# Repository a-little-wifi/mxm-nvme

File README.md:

# MXM NVMe

I made an MXM edge connector footprint and wanted to make a board that uses it so I can make some screenshots, so here's a crappy unfinished concept for a board that lets you use one or maybe more NVMe SSDs in an MXM slot. Currently wired for x8x4x4 bifurcation mode.

Feel free to take the MXM edge connector footprint from it.

## Here's some pictures
<!------>

I didn't do impedance matching or anything yet, the diffpairs are just there to look pretty ✨

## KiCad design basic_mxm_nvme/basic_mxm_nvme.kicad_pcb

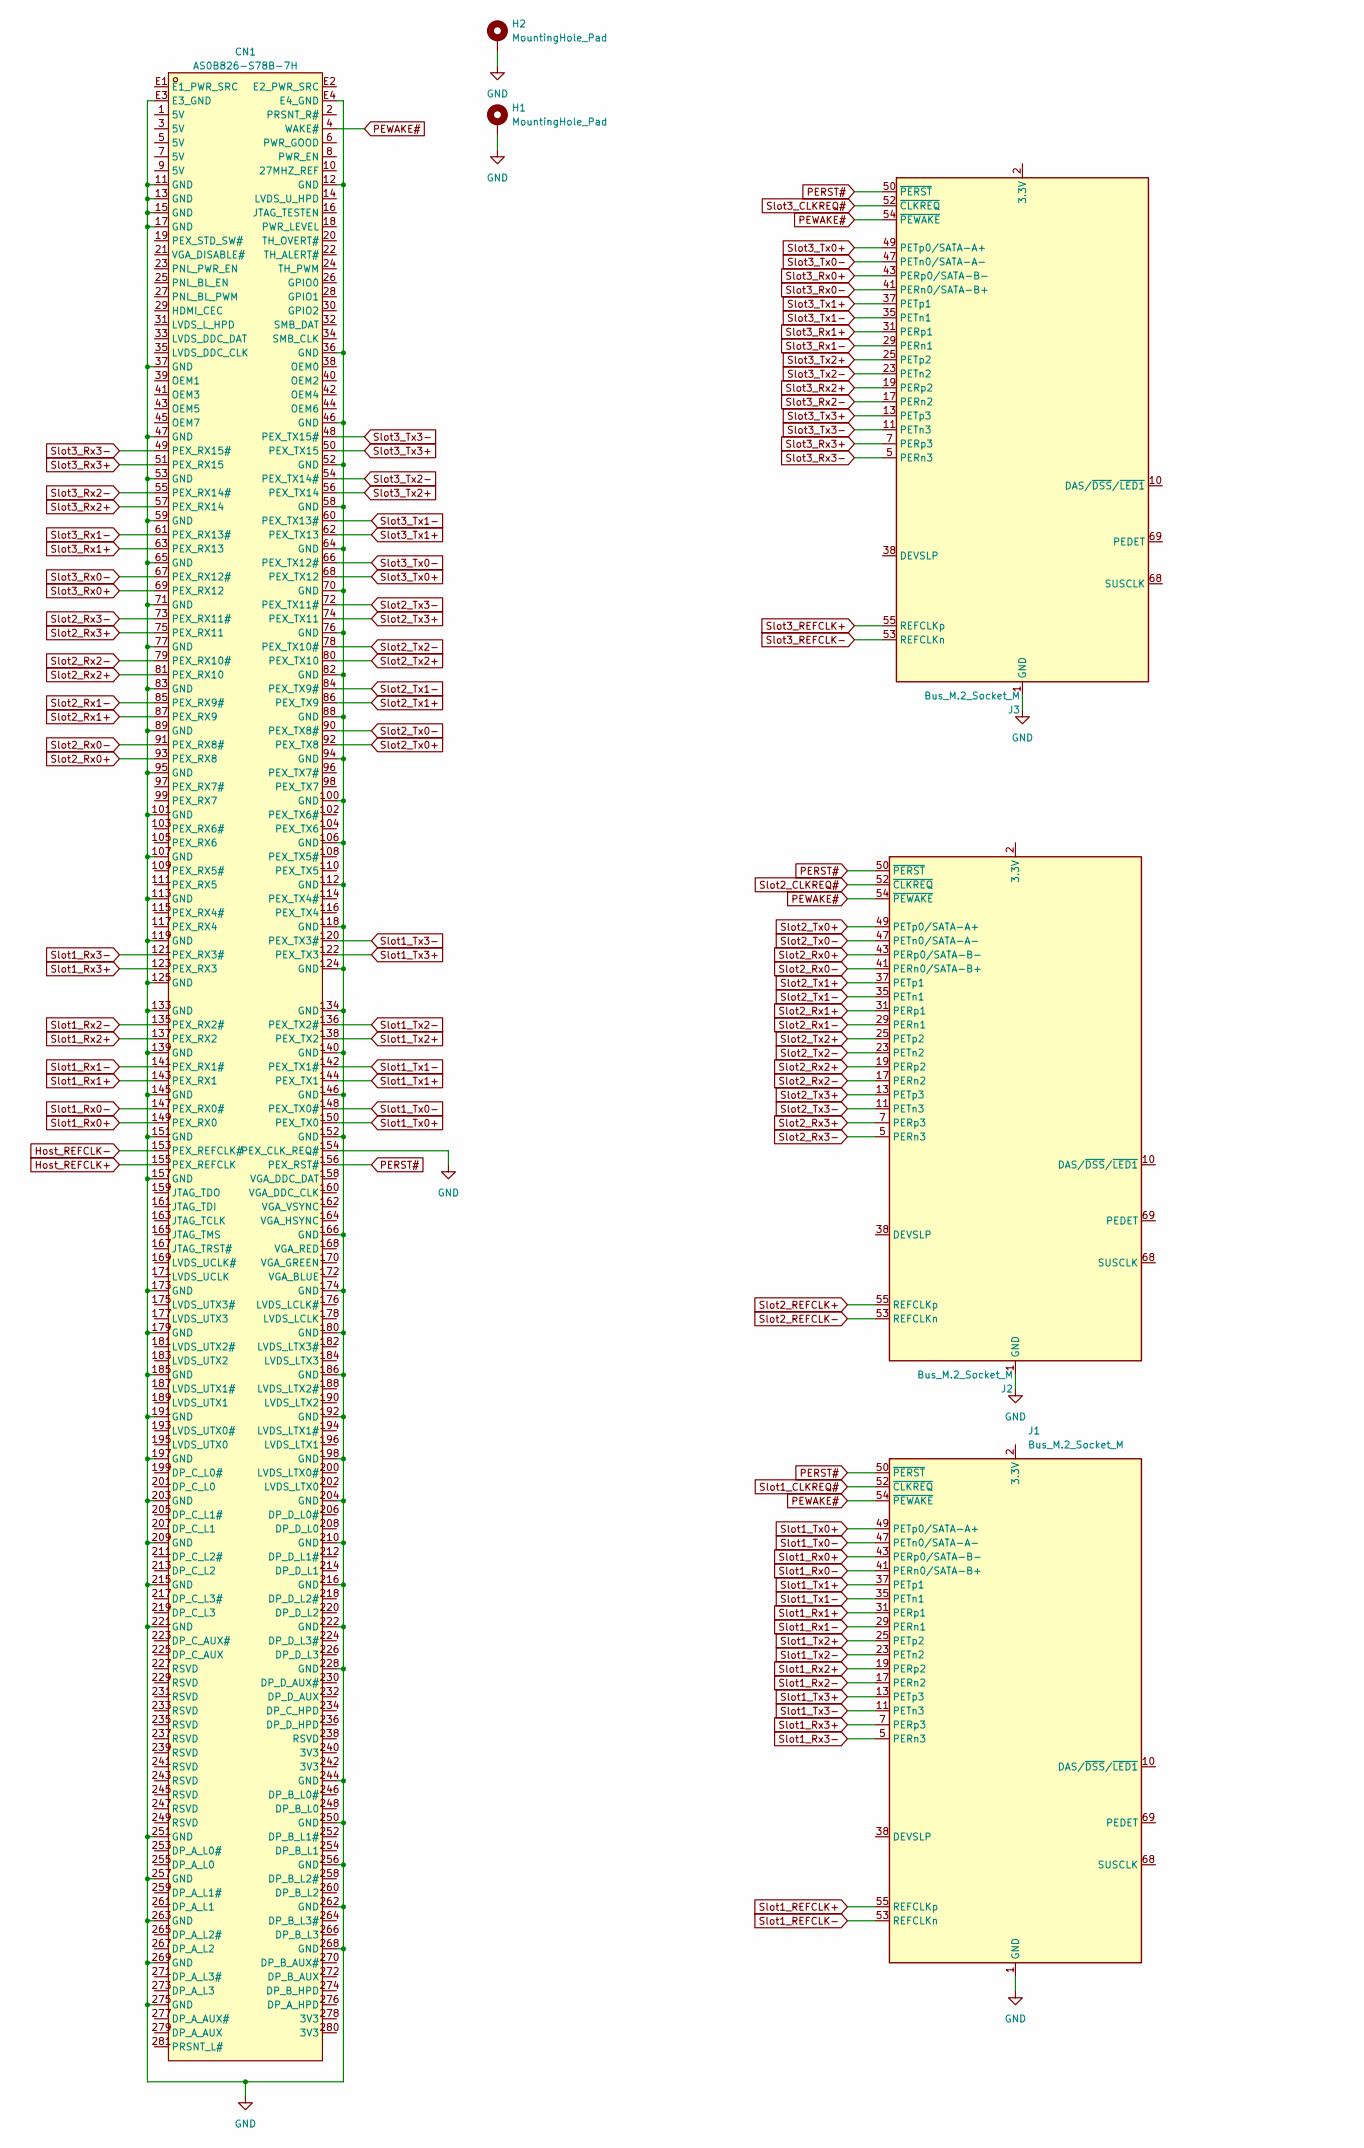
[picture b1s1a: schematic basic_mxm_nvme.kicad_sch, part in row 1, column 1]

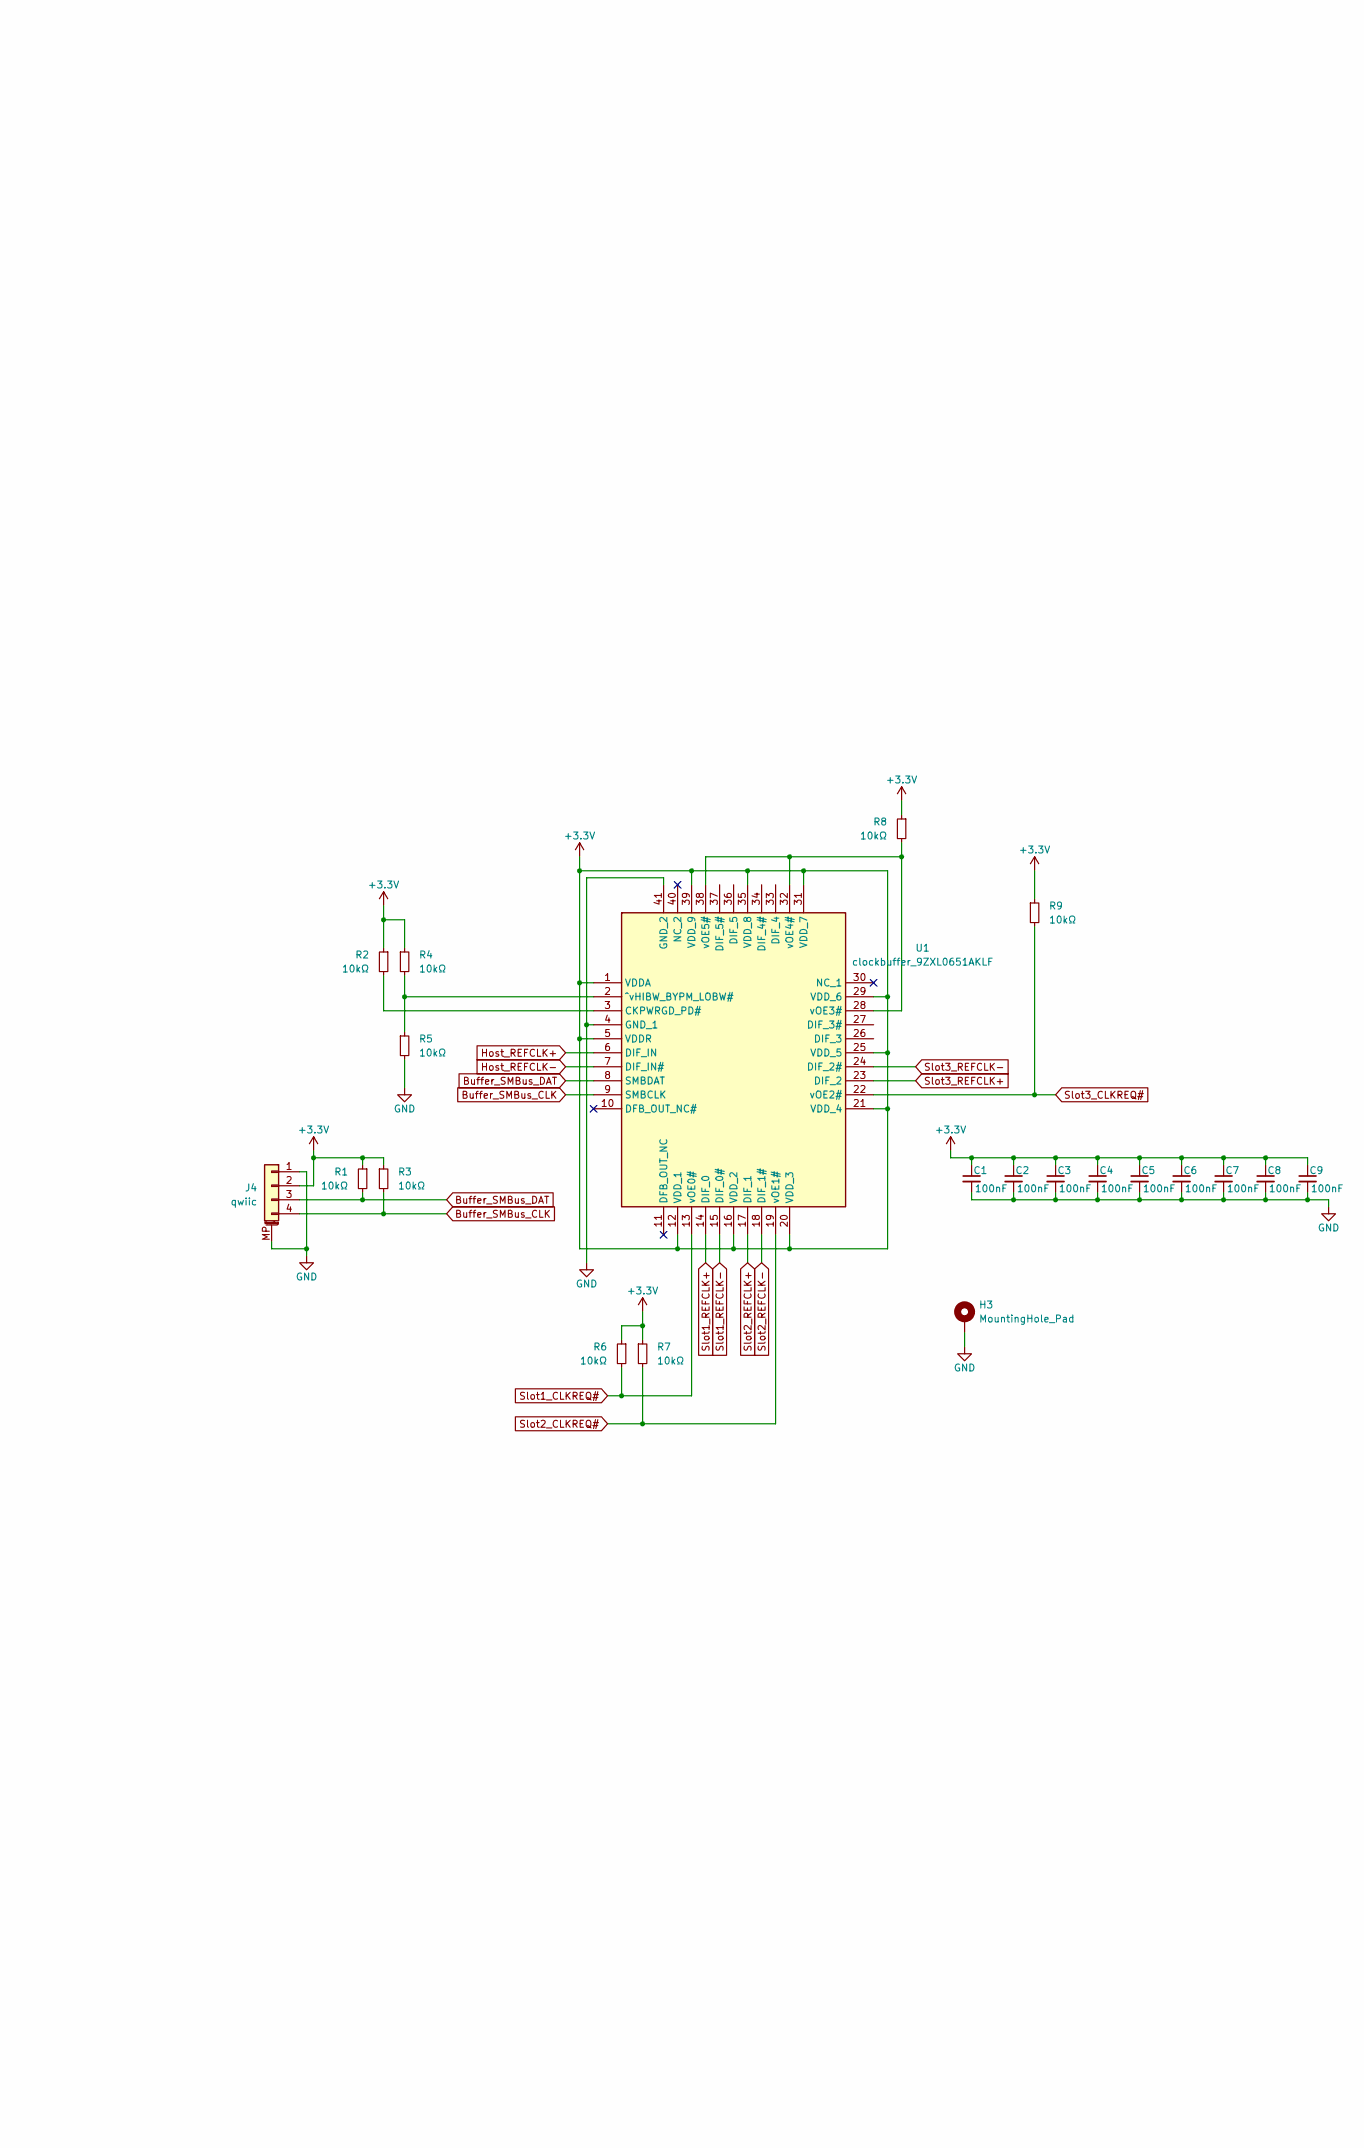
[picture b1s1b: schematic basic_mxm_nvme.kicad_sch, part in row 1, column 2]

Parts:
C1, C2, C3, C4, C5, C6, C7, C8, C9: 100nF; C_0603_1608Metric
CN1: AS0B826-S78B-7H; MXM-edge; LCSC Part C426232
H1, H2: MountingHole_Pad; MountingHole_3.2mm_M3_DIN965_Pad_TopBottom
H3: MountingHole_Pad; TestPoint_THTPad_D3.0mm_Drill1.5mm
J1, J2, J3: Bus_M.2_Socket_M; m-key
J4: qwiic; JST_SH_SM04B-SRSS-TB_1x04-1MP_P1.00mm_Horizontal
R1, R2, R3, R4, R5, R6, R7, R8, R9: 10kΩ; R_0603_1608Metric
U1: clockbuffer_9ZXL0651AKLF; Manufacturer_Part_Number 9ZXL0651AKLF

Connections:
+3.3V: C1.1, C2.1, C3.1, C4.1, C5.1, C6.1, C7.1, C8.1, C9.1, J4.2, R1.1, R2.1, R3.1, R4.1, R6.1, R7.1, R8.1, R9.1, U1.1 (VDDA), U1.5 (VDDR), U1.12 (VDD_1), U1.16 (VDD_2), U1.20 (VDD_3), U1.21 (VDD_4), U1.25 (VDD_5), U1.29 (VDD_6), U1.31 (VDD_7), U1.35 (VDD_8), U1.39 (VDD_9)
Buffer_SMBus_CLK: J4.4, R3.2, U1.9 (SMBCLK)
Buffer_SMBus_DAT: J4.3, R1.2, U1.8 (SMBDAT)
GND: C1.2, C2.2, C3.2, C4.2, C5.2, C6.2, C7.2, C8.2, C9.2, CN1.11 (GND), CN1.12 (GND), CN1.13 (GND), CN1.15 (GND), CN1.17 (GND), CN1.36 (GND), CN1.37 (GND), CN1.46 (GND), CN1.47 (GND), CN1.52 (GND), CN1.53 (GND), CN1.58 (GND), CN1.59 (GND), CN1.64 (GND), CN1.65 (GND), CN1.70 (GND), CN1.71 (GND), CN1.76 (GND), CN1.77 (GND), CN1.82 (GND), CN1.83 (GND), CN1.88 (GND), CN1.89 (GND), CN1.94 (GND), CN1.95 (GND), CN1.100 (GND), CN1.101 (GND), CN1.106 (GND), CN1.107 (GND), CN1.112 (GND), CN1.113 (GND), CN1.118 (GND), CN1.119 (GND), CN1.124 (GND), CN1.125 (GND), CN1.133 (GND), CN1.134 (GND), CN1.139 (GND), CN1.140 (GND), CN1.145 (GND), CN1.146 (GND), CN1.151 (GND), CN1.152 (GND), CN1.154 (PEX_CLK_REQ#), CN1.157 (GND), CN1.166 (GND), CN1.173 (GND), CN1.174 (GND), CN1.179 (GND), CN1.180 (GND), CN1.185 (GND), CN1.186 (GND), CN1.191 (GND), CN1.192 (GND), CN1.197 (GND), CN1.198 (GND), CN1.203 (GND), CN1.204 (GND), CN1.209 (GND), CN1.210 (GND), CN1.215 (GND), CN1.216 (GND), CN1.221 (GND), CN1.222 (GND), CN1.228 (GND), CN1.244 (GND), CN1.250 (GND), CN1.251 (GND), CN1.256 (GND), CN1.257 (GND), CN1.262 (GND), CN1.263 (GND), CN1.268 (GND), CN1.269 (GND), CN1.275 (GND), CN1.E3 (E3_GND), CN1.E4 (E4_GND), H1.1, H2.1, H3.1, J1.1 (GND), J1.3 (GND), J1.9 (GND), J1.15 (GND), J1.21 (GND), J1.27 (GND), J1.33 (GND), J1.39 (GND), J1.45 (GND), J1.51 (GND), J1.57 (GND), J1.71 (GND), J1.73 (GND), J1.75 (GND), J2.1 (GND), J2.3 (GND), J2.9 (GND), J2.15 (GND), J2.21 (GND), J2.27 (GND), J2.33 (GND), J2.39 (GND), J2.45 (GND), J2.51 (GND), J2.57 (GND), J2.71 (GND), J2.73 (GND), J2.75 (GND), J3.1 (GND), J3.3 (GND), J3.9 (GND), J3.15 (GND), J3.21 (GND), J3.27 (GND), J3.33 (GND), J3.39 (GND), J3.45 (GND), J3.51 (GND), J3.57 (GND), J3.71 (GND), J3.73 (GND), J3.75 (GND), J4.1, J4.MP (MountPin), R5.2, U1.4 (GND_1), U1.41 (GND_2)
Host_REFCLK+: CN1.155 (PEX_REFCLK), U1.6 (DIF_IN)
Host_REFCLK-: CN1.153 (PEX_REFCLK#), U1.7 (DIF_IN#)
unnamed: J1.2 (3.3V), J1.4 (3.3V), J1.12 (3.3V), J1.14 (3.3V), J1.16 (3.3V), J1.18 (3.3V), J1.70 (3.3V), J1.72 (3.3V), J1.74 (3.3V)
unnamed: J2.2 (3.3V), J2.4 (3.3V), J2.12 (3.3V), J2.14 (3.3V), J2.16 (3.3V), J2.18 (3.3V), J2.70 (3.3V), J2.72 (3.3V), J2.74 (3.3V)
unnamed: J3.2 (3.3V), J3.4 (3.3V), J3.12 (3.3V), J3.14 (3.3V), J3.16 (3.3V), J3.18 (3.3V), J3.70 (3.3V), J3.72 (3.3V), J3.74 (3.3V)
unnamed: R2.2, U1.3 (CKPWRGD_PD#)
unnamed: R4.2, R5.1, U1.2 (^vHIBW_BYPM_LOBW#)
unnamed: R8.2, U1.28 (vOE3#), U1.32 (vOE4#), U1.38 (vOE5#)
PERST#: CN1.156 (PEX_RST#), J1.50 (~PERST), J2.50 (~PERST), J3.50 (~PERST)
PEWAKE#: CN1.4 (WAKE#), J1.54 (~PEWAKE), J2.54 (~PEWAKE), J3.54 (~PEWAKE)
Slot1_CLKREQ#: J1.52 (~CLKREQ), R6.2, U1.13 (vOE0#)
Slot1_REFCLK+: J1.55 (REFCLKp), U1.14 (DIF_0)
Slot1_REFCLK-: J1.53 (REFCLKn), U1.15 (DIF_0#)
Slot1_Rx0+: CN1.149 (PEX_RX0), J1.43 (PERp0/SATA-B-)
Slot1_Rx0-: CN1.147 (PEX_RX0#), J1.41 (PERn0/SATA-B+)
Slot1_Rx1+: CN1.143 (PEX_RX1), J1.31 (PERp1)
Slot1_Rx1-: CN1.141 (PEX_RX1#), J1.29 (PERn1)
Slot1_Rx2+: CN1.137 (PEX_RX2), J1.19 (PERp2)
Slot1_Rx2-: CN1.135 (PEX_RX2#), J1.17 (PERn2)
Slot1_Rx3+: CN1.123 (PEX_RX3), J1.7 (PERp3)
Slot1_Rx3-: CN1.121 (PEX_RX3#), J1.5 (PERn3)
Slot1_Tx0+: CN1.150 (PEX_TX0), J1.49 (PETp0/SATA-A+)
Slot1_Tx0-: CN1.148 (PEX_TX0#), J1.47 (PETn0/SATA-A-)
Slot1_Tx1+: CN1.144 (PEX_TX1), J1.37 (PETp1)
Slot1_Tx1-: CN1.142 (PEX_TX1#), J1.35 (PETn1)
Slot1_Tx2+: CN1.138 (PEX_TX2), J1.25 (PETp2)
Slot1_Tx2-: CN1.136 (PEX_TX2#), J1.23 (PETn2)
Slot1_Tx3+: CN1.122 (PEX_TX3), J1.13 (PETp3)
Slot1_Tx3-: CN1.120 (PEX_TX3#), J1.11 (PETn3)
Slot2_CLKREQ#: J2.52 (~CLKREQ), R7.2, U1.19 (vOE1#)
Slot2_REFCLK+: J2.55 (REFCLKp), U1.17 (DIF_1)
Slot2_REFCLK-: J2.53 (REFCLKn), U1.18 (DIF_1#)
Slot2_Rx0+: CN1.93 (PEX_RX8), J2.43 (PERp0/SATA-B-)
Slot2_Rx0-: CN1.91 (PEX_RX8#), J2.41 (PERn0/SATA-B+)
Slot2_Rx1+: CN1.87 (PEX_RX9), J2.31 (PERp1)
Slot2_Rx1-: CN1.85 (PEX_RX9#), J2.29 (PERn1)
Slot2_Rx2+: CN1.81 (PEX_RX10), J2.19 (PERp2)
Slot2_Rx2-: CN1.79 (PEX_RX10#), J2.17 (PERn2)
Slot2_Rx3+: CN1.75 (PEX_RX11), J2.7 (PERp3)
Slot2_Rx3-: CN1.73 (PEX_RX11#), J2.5 (PERn3)
Slot2_Tx0+: CN1.92 (PEX_TX8), J2.49 (PETp0/SATA-A+)
Slot2_Tx0-: CN1.90 (PEX_TX8#), J2.47 (PETn0/SATA-A-)
Slot2_Tx1+: CN1.86 (PEX_TX9), J2.37 (PETp1)
Slot2_Tx1-: CN1.84 (PEX_TX9#), J2.35 (PETn1)
Slot2_Tx2+: CN1.80 (PEX_TX10), J2.25 (PETp2)
Slot2_Tx2-: CN1.78 (PEX_TX10#), J2.23 (PETn2)
Slot2_Tx3+: CN1.74 (PEX_TX11), J2.13 (PETp3)
Slot2_Tx3-: CN1.72 (PEX_TX11#), J2.11 (PETn3)
Slot3_CLKREQ#: J3.52 (~CLKREQ), R9.2, U1.22 (vOE2#)
Slot3_REFCLK+: J3.55 (REFCLKp), U1.23 (DIF_2)
Slot3_REFCLK-: J3.53 (REFCLKn), U1.24 (DIF_2#)
Slot3_Rx0+: CN1.69 (PEX_RX12), J3.43 (PERp0/SATA-B-)
Slot3_Rx0-: CN1.67 (PEX_RX12#), J3.41 (PERn0/SATA-B+)
Slot3_Rx1+: CN1.63 (PEX_RX13), J3.31 (PERp1)
Slot3_Rx1-: CN1.61 (PEX_RX13#), J3.29 (PERn1)
Slot3_Rx2+: CN1.57 (PEX_RX14), J3.19 (PERp2)
Slot3_Rx2-: CN1.55 (PEX_RX14#), J3.17 (PERn2)
Slot3_Rx3+: CN1.51 (PEX_RX15), J3.7 (PERp3)
Slot3_Rx3-: CN1.49 (PEX_RX15#), J3.5 (PERn3)
Slot3_Tx0+: CN1.68 (PEX_TX12), J3.49 (PETp0/SATA-A+)
Slot3_Tx0-: CN1.66 (PEX_TX12#), J3.47 (PETn0/SATA-A-)
Slot3_Tx1+: CN1.62 (PEX_TX13), J3.37 (PETp1)
Slot3_Tx1-: CN1.60 (PEX_TX13#), J3.35 (PETn1)
Slot3_Tx2+: CN1.56 (PEX_TX14), J3.25 (PETp2)
Slot3_Tx2-: CN1.54 (PEX_TX14#), J3.23 (PETn2)
Slot3_Tx3+: CN1.50 (PEX_TX15), J3.13 (PETp3)
Slot3_Tx3-: CN1.48 (PEX_TX15#), J3.11 (PETn3)

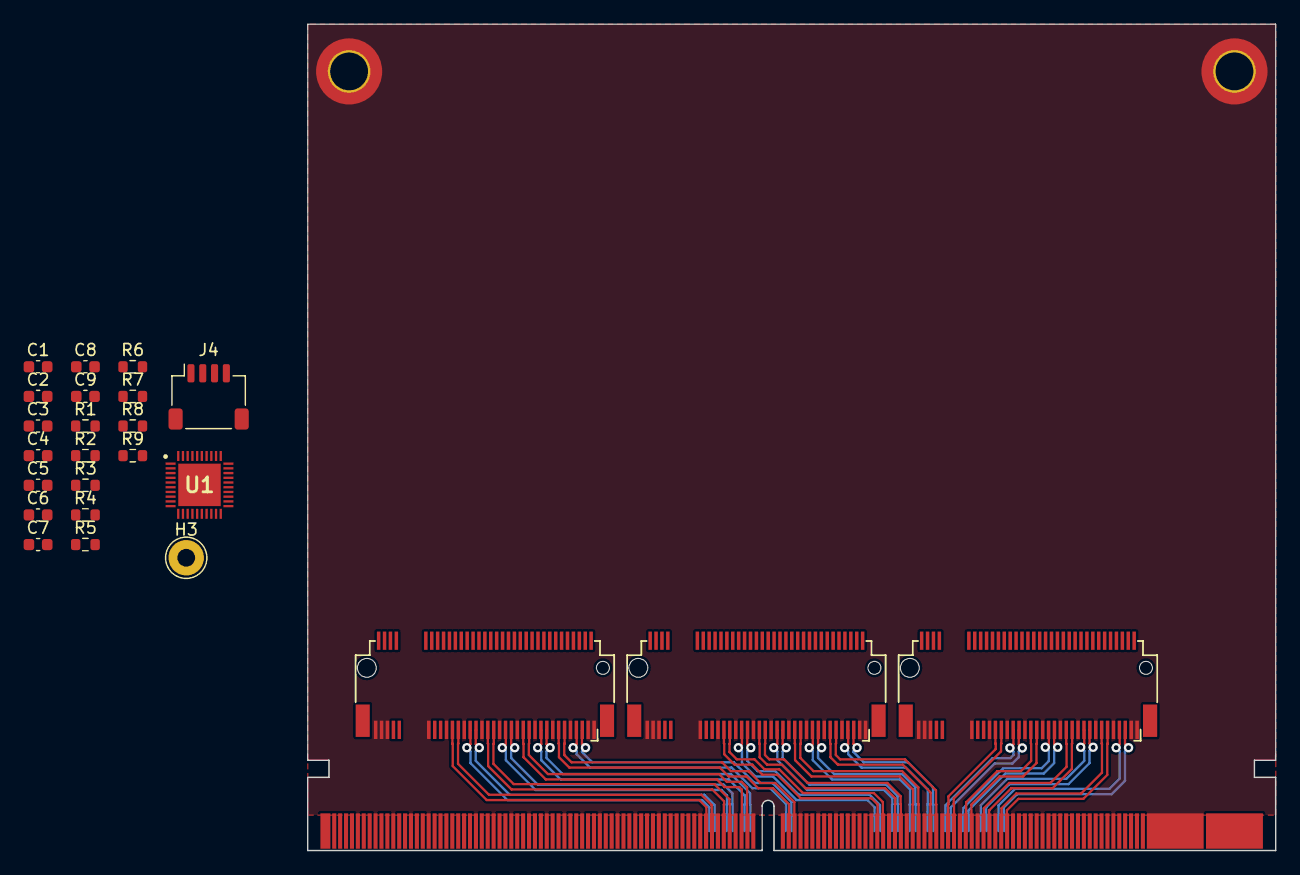
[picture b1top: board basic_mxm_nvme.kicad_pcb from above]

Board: 2 copper layers, 82.0 x 70.0 mm, 27 parts (0 on the bottom side), 71 nets.

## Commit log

2024-02-11 Added the files
    Hella unfinished but it's here now lol
2024-02-11 Updated gitignore for lock files
2024-02-11 Added picture to readme
2024-02-11 Made picture in readme smaller
2024-02-11 Added another picture
2024-02-11 reformatted pictures
    they don't show up next to each other on github
2024-02-15 Added type marks to footprint
2024-11-02 Added clock buffer to schematic
    and put the footprints in the pcb file
